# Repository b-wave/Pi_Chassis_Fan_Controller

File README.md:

# A Pi Chassis Fan Controller - Interface Board 
This describes a small board to interface a 5V, 4-wire fan in a controller cabinet with a Raspberry Pi controller.  The fan I am using is a **GeeekPi** 40x40x10mm 4-wire Fan, **Model F-0028**.  [https://www.amazon.com/GeeekPi-Raspberry-40x40x10mm-Adjustment-Included/dp/B0CL41RG93] 

The JST SH connector on the board should be compatible with the Raspberry Pi's Fan Connector. But that connector did not exist on a PI3. You **DO NOT** need this board to control the processor fan, it is intended to actively ventilate an enclosed, wall mounted cabinet. Yes, it is over-designed and has extras such as a static ring ground and ESD diodes - all are probably overkill but it is cheap insurance.  Yes, there are three revisions. I started with a two-wire fan, then three-wire, and finally with this 4-wire version with 100% less transistors.  It mainly just converts the short JST connector into a standard screw terminal. 

Although I provide a separate 2-pin input voltage connector terminal block (J3) it is intended for 5-Volts only. Its purpose is to not stress the **Raspberry Pi's** Power supply.  Although it should be perfectly fine to run the recommended fan directly off of the +5V, since it was designed to run off of the fan connector on the newer boards. 

By the way, that connector is reverse voltage protected in case you get the power leads reversed - you *should not* damage the Pi.

<h2 align="center">⚡ CAUTION ⚡</h2>

Be careful if using a 12V fan! *Damage may occur to 3v3 inputs and you may fry your Pi* 

It may need a **level shifter** if it does not provide 5V or pin compatible signals (TACH and maybe the PWM) - verify pin voltages before connecting to PI.  If they are open collector, the 3v3 reference on the 10k pullup should take care of that. 

## Overview
I am working on a Raspberry Pi 4 controlled LTE gateway using a small DIN rail enclosure.  The planned locations are at fairly remote, and the equipment will be enclosed in a small cabinet so active ventilation is required.  This board was needed to simplify installation and to provide some visual and remote feedback.  This is a fairly simple board that is tailored to my specific installations, but I may expand it to be more general purpose.  In any case, it provides a neat interface to control a cabinet fan I finally settled on this design:

The schematic is pretty straightforward.  It uses a hybrid SMT + Through-hole technologies. The ESD diodes wee exceedingly hard to hand solder *so I left them off the prototype,* but the rest of the board should be OK.  

---

## Hardware Description
The hardware combines familiar building blocks with some added protection from the very warm (hot) and dry environment.   I may put ESD tape and spray in my enclosure as it is intended to run in a dry dusty environment. 

  *I am not 100% sure if the "Ring Ground" is implemented correctly.  ...But it looks cool?*

It is a approximately one inch square and is designed to fit on a small DIN rail carrier. The board is available on OSHPARK Shared and I will leave a link. [ www.oshpark](https://oshpark.com) ~The shown image is an early version and some components are moved. I will update and add a link after testing!~  

            Hole Spacing: 0.75" x 0.80" (19.0mm x 20.3mm)
            Board Outline: 1.10" x 1.20" (27.6mm x 30.2 mm)

  - The LEDs give a visual indication of the fan's operation, since in many cases the fan cannot be seen or heard. 

### Wiring: 
The fan controller interface board was designed with screw blocks so you can use wires (stranded 20-22 AWG is recommend) simply strip your wire tips back ~1/8", slide them into the screw terminals, and screw to clamp them down tightly. Alternately, DuPont jumper wires should work, acting like ferrules to keep the wires from pinching. Since these connectors are on 0.1" (2.54mm) centers so you can alternately use regular pin headers and DuPont jumpers.

### Input connector: 
This connector should be compatible with most 4-wire 5V cooling fans. It helps in two ways. First you just plug in the fan, it provides an interface for the fan's connector. Secondly, since this board is meant for use in an enclosure, the fan wires usually are not long enough, so simply locate this board near the fan and run longer wires back to the Pi.

### Power Connector: 
J3 pins may be used to input power for the fan. A second external power supply may be used to keep load off of the 5V Raspberry power supply. An external 5V supply should be used but it is possible to use a 12V fan but be mindful of the signals (TACH and PWM) may not have GPIO compatible levels.  But typically the TACH signal is an open collector (or Drain) type so you can use the pull up and the 3v3 reference will generate the proper input signal.  

 - Fan 5V Power (J3) Pin (1) (Red) ──► Screw into terminal 5V (Pin 2 or 4)
 - Fan 5V Ground (J3) Pin (2) (Black) ──► Screw into terminal GND (Pin 6, 9, or 14)
   *Or use an external 5V supply* 

### Signal Pins: 
J2 is the signal interface to the Raspberry PI's GPIOs needed to control and monitor the fan. Two GPIOs are needed, one output for the **PWM** and input for the **TAC (FG)** wires. 

 - Fan 3 Volt Reference (RED) ──► Screw into terminal (3V3)
 - Fan PWM Control Signal (Blue) ──► Screw into terminal GPIO 12 (Pin 32)
 - Fan System Ground (Black) ──► Screw into terminal GND (Pin 6, 9, or 14)
 - Fan TACH (or FG) Speed Feedback (Yellow) ──► Screw into terminal GPIO 13 (Pin 33)
  
    - **NOTE:**
      - The wire colors are fairly standard - but they should match the Pi-Fan connectors
      - If the PWM wire connection is open the fan will run at full speed. If you don't want that put a large (10k - 100k) resistor to ground 

### The "ON" LED: 
      
The "Fan On" or "Drive" Indicator (Green or Red)

This LED is wired to the PWM lines powering the fan. When the fan is running at full speed (100% PWM) it is ON full, when it is OFF ( 0% PWM) the fan is OFF. There is a slight dim glow green whenever the fan has power and is being driven by the PWM signal in different speeds it also changes brightness. 

  - **NOTE:** This LED can also be used to FLASH a code if the fan stalls to aid in servicing since it is strictly an output. 
  
### The "RUN" LED: 
The "Fan Spinning" Indicator (Yellow or Blue). 

This LED is wired to the TACH  line to monitor it visually. Sometimes this signal is labeled Frequency Generator (FG). 

When the fan is stalled or off, the LED either stays solid or completely dark. When the fan spins at high speed (e.g., 3000 RPM), the TACH pulses occur so quickly (100 times per second) that human eyes perceive the flashing as a continuous, soft glow. If the fan slows down or begins to struggle, you will visually notice the light dimming or starting to flicker.  If it stops with the LED ON it will turn off after a few seconds. this is normal behavior of these fans to protect against a stall it shuts the control circuits down.  It may even flash occasionally on some fans to test to see if the obstruction is clear. 

---

## Example Software

*Coming Soon! - no, really.  Check back*

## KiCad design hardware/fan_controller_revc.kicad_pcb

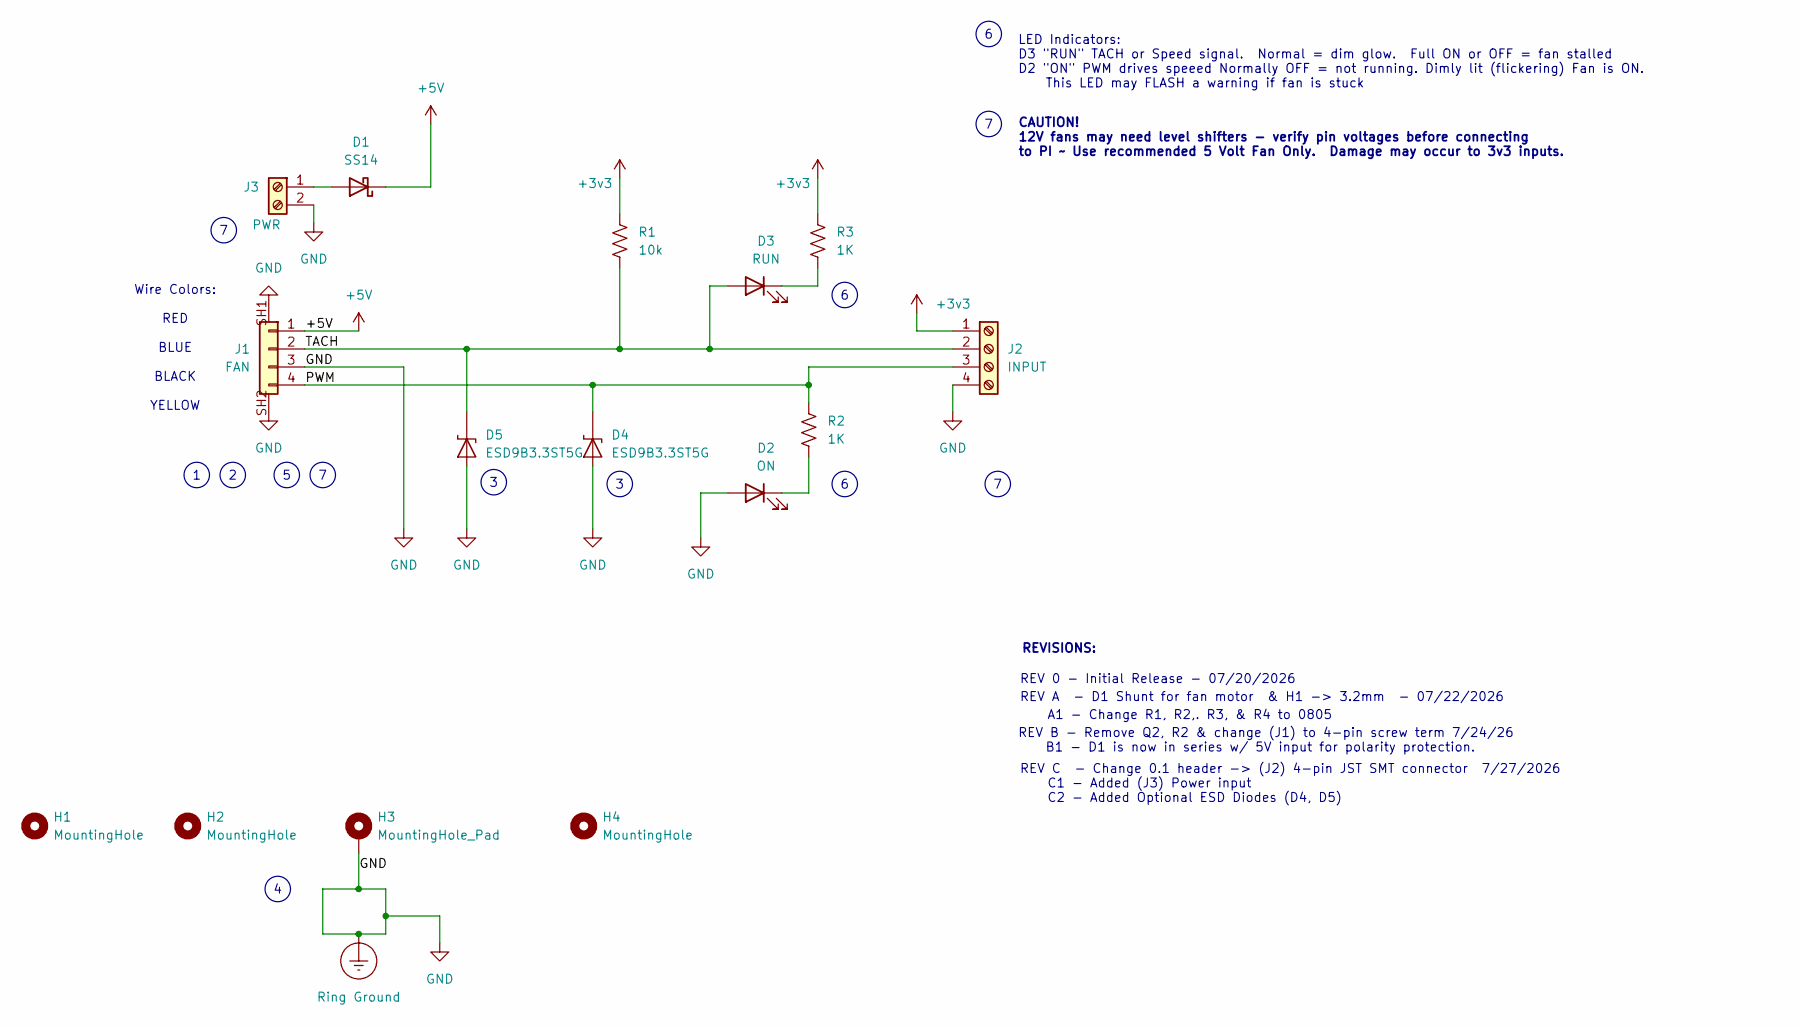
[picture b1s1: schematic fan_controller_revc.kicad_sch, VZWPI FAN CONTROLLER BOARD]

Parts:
D1: SS14; D_SMA
D2: ON; LED_0805_2012Metric_Pad1.15x1.40mm_HandSolder
D3: RUN; LED_0805_2012Metric_Pad1.15x1.40mm_HandSolder
D4, D5: ESD9B3.3ST5G; D_SOD-923
H1, H2, H4: MountingHole; MountingHole_3.2mm_M3_DIN965
H3: MountingHole_Pad; MountingHole_3.2mm_M3_Pad_Via
J1: FAN; ADAFRUIT_4328
J2: INPUT; TerminalBlock_Phoenix_MPT-0,5-4-2.54_1x04_P2.54mm_Horizontal
J3: PWR; TerminalBlock_Phoenix_MPT-0,5-2-2.54_1x02_P2.54mm_Horizontal
R1: 10k; R_0805_2012Metric_Pad1.20x1.40mm_HandSolder
R2, R3: 1K; R_0805_2012Metric_Pad1.20x1.40mm_HandSolder

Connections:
+3v3: J2.1, R1.1, R3.1
+5V: D1.1 (K), J1.1
/PWM: D4.1 (k), J1.4, J2.3, R2.2
/TACH: D3.2 (A), D5.1 (k), J1.2, J2.2, R1.2
GND: D2.2 (A), D4.2 (k), D5.2 (k), H3.1, J1.3, J1.SH1, J1.SH2, J2.4, J3.2
unnamed: D1.2 (A), J3.1
unnamed: D2.1 (K), R2.1
unnamed: D3.1 (K), R3.2

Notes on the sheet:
Wire Colors: RED BLUE BLACK YELLOW
A1 - Change R1, R2,. R3, & R4 to 0805
REVISIONS:
REV C - Change 0.1 header -> (J2) 4-pin JST SMT connector 7/27/2026 C1 - Added (J3) Power input C2 - Added Optional ESD Diodes (D4, D5)
LED Indicators: D3 "RUN" TACH or Speed signal. Normal = dim glow. Full ON or OFF = fan stalled D2 "ON" PWM drives speeed Normally OFF = not running. Dimly lit (flickering) Fan is ON. This LED may FLASH a warning if fan is stuck
REV 0 - Initial Release - 07/20/2026
REV A - D1 Shunt for fan motor & H1 -> 3.2mm - 07/22/2026
REV B - Remove Q2, R2 & change (J1) to 4-pin screw term 7/24/26 B1 - D1 is now in series w/ 5V input for polarity protection.
CAUTION! 12V fans may need level shifters - verify pin voltages before connecting to PI ~ Use recommended 5 Volt Fan Only. Damage may occur to 3v3 inputs.

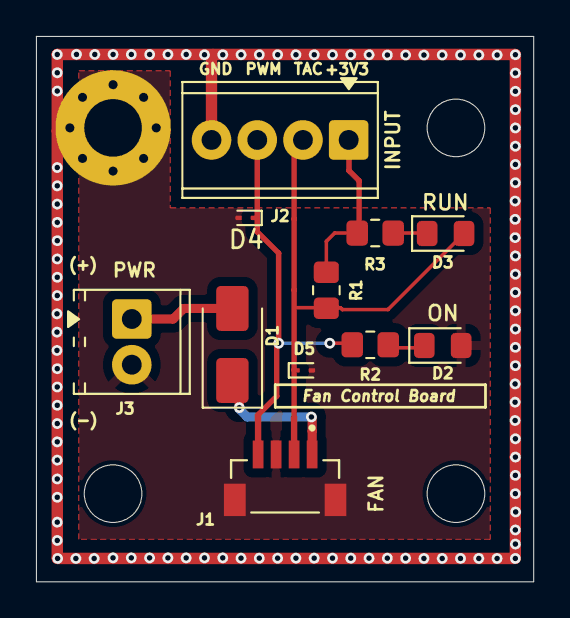
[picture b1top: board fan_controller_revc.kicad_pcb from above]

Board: 2 copper layers, 27.6 x 30.3 mm, 15 parts (0 on the bottom side), 8 nets.
